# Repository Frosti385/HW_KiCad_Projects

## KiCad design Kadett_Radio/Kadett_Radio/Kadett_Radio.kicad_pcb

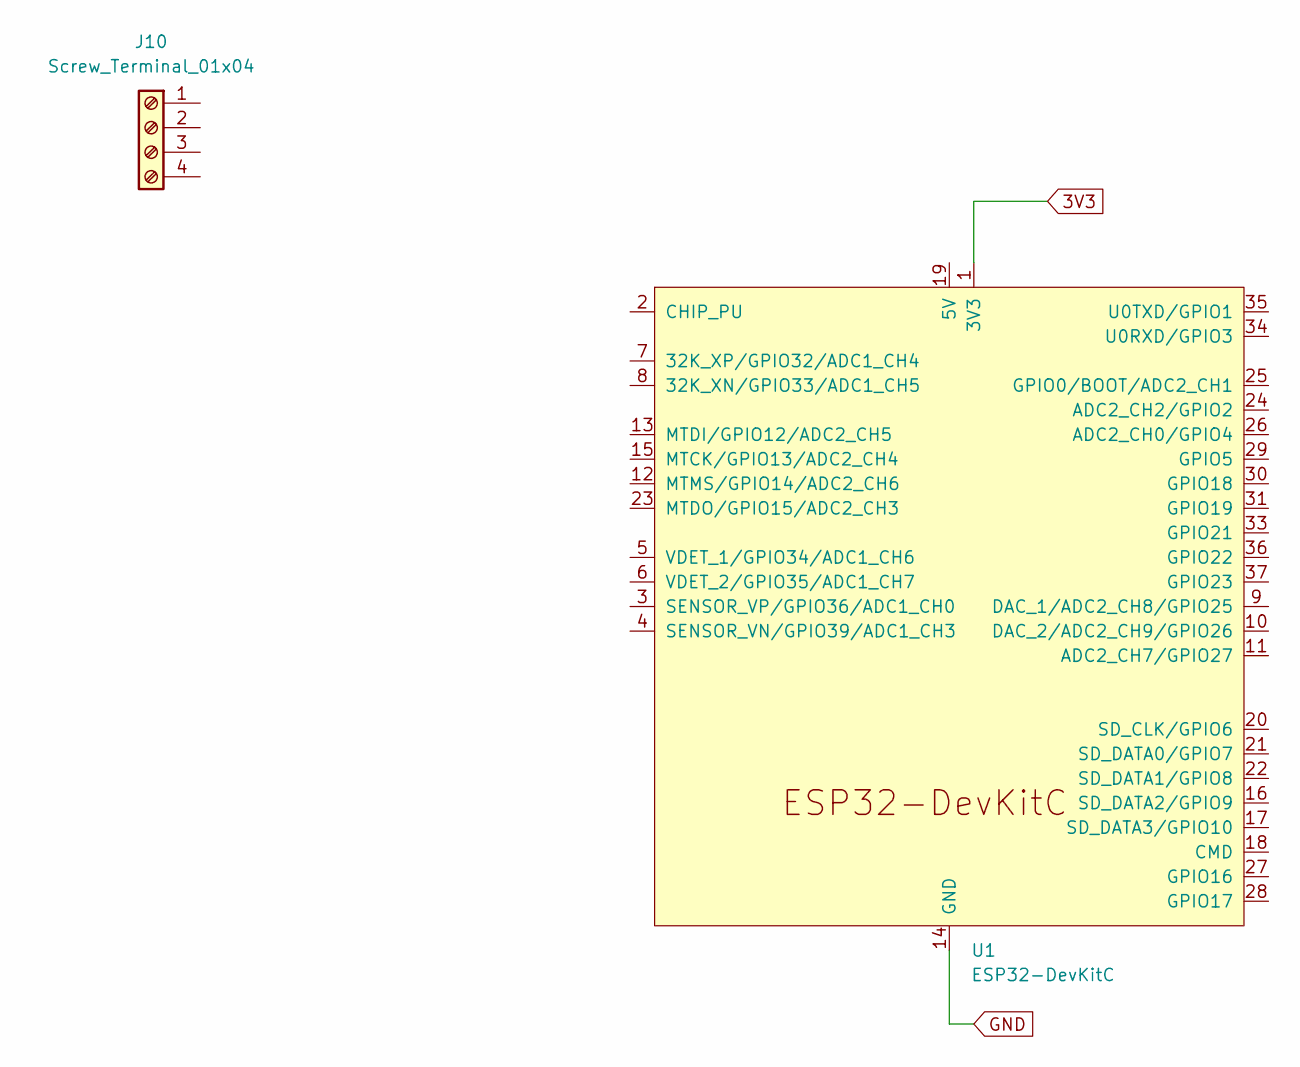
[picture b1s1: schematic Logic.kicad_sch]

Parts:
J10: Screw_Terminal_01x04; TerminalBlock_Phoenix_MPT-0,5-4-2.54_1x04_P2.54mm_Horizontal
U1: ESP32-DevKitC

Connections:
3V3: U1.1 (3V3); also elsewhere on the board
GND: U1.14 (GND), U1.32 (GND), U1.38 (GND); also elsewhere on the board

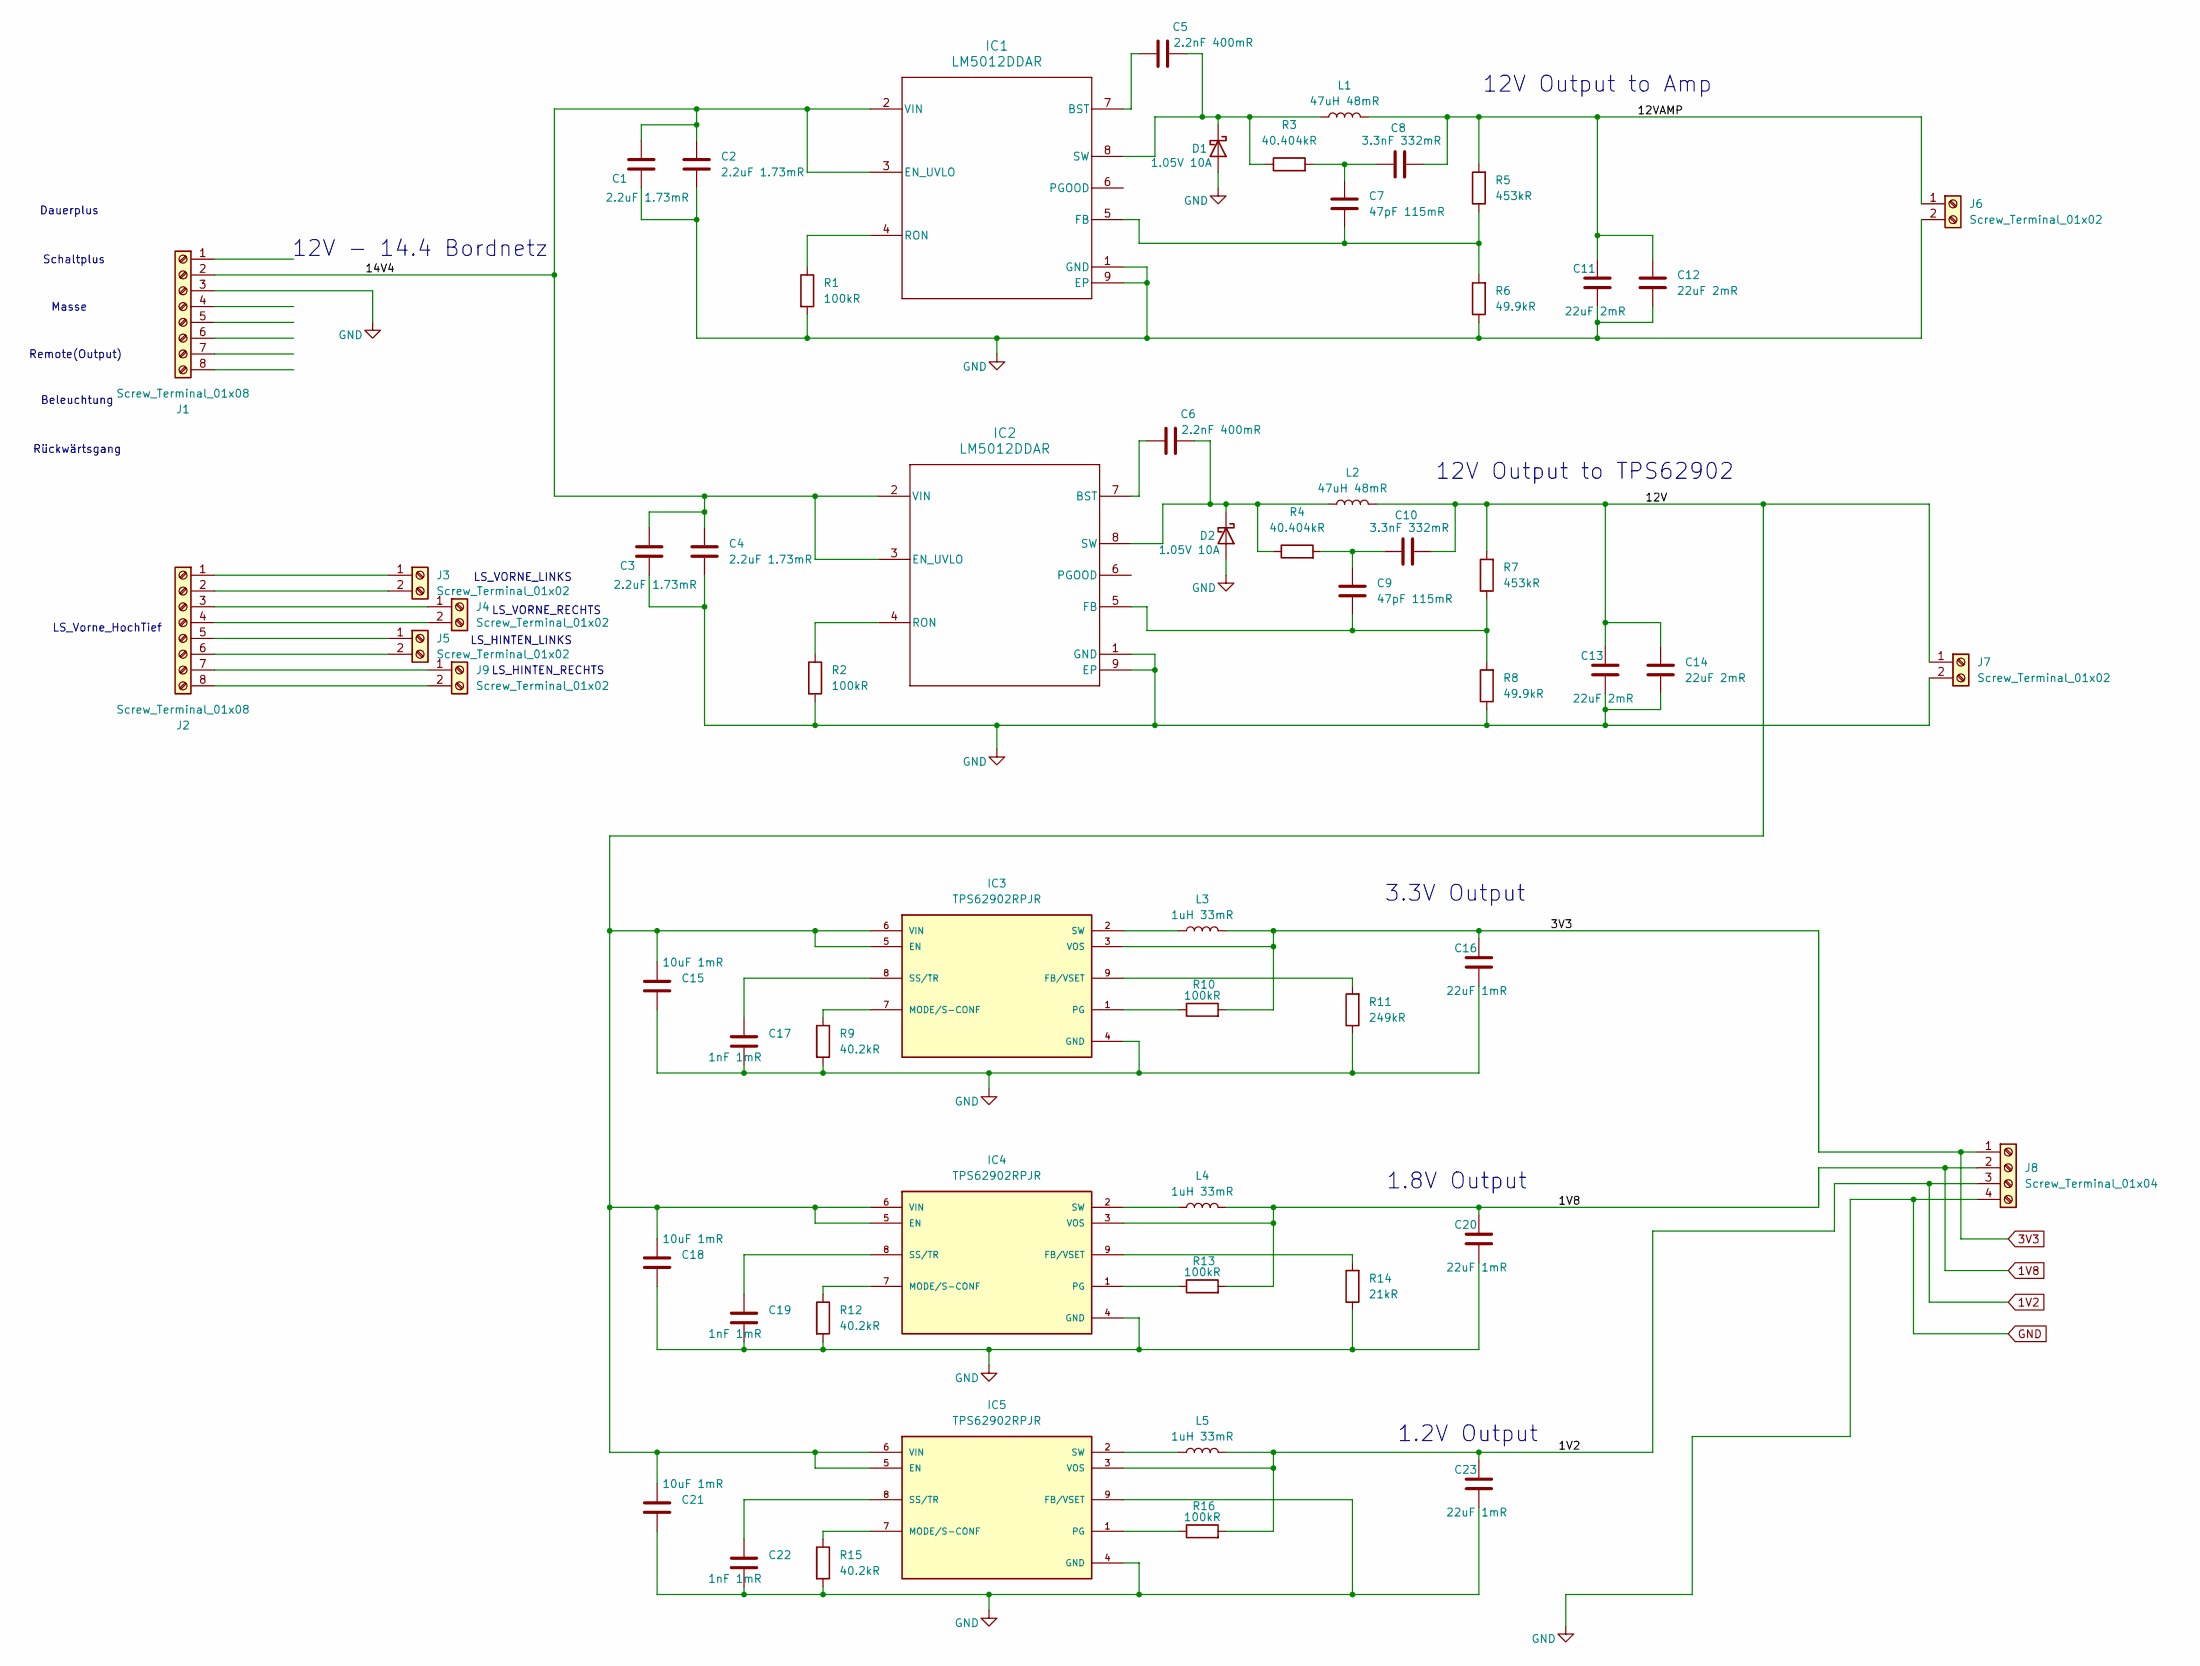
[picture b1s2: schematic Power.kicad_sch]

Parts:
C1, C2, C3, C4: 2.2uF 1.73mR; C_0603_1608Metric_Pad1.08x0.95mm_HandSolder
C5, C6: 2.2nF 400mR; C_0603_1608Metric_Pad1.08x0.95mm_HandSolder
C7, C9: 47pF 115mR; C_0603_1608Metric_Pad1.08x0.95mm_HandSolder
C8, C10: 3.3nF 332mR; C_0603_1608Metric_Pad1.08x0.95mm_HandSolder
C11, C12, C13, C14: 22uF 2mR; C_0603_1608Metric_Pad1.08x0.95mm_HandSolder
C15, C18, C21: 10uF 1mR; C_0603_1608Metric_Pad1.08x0.95mm_HandSolder
C16, C20, C23: 22uF 1mR; C_0603_1608Metric_Pad1.08x0.95mm_HandSolder
C17, C19, C22: 1nF 1mR; C_0603_1608Metric_Pad1.08x0.95mm_HandSolder
D1, D2: 1.05V 10A; D_0603_1608Metric_Pad1.05x0.95mm_HandSolder
IC1, IC2: LM5012DDAR; LM5012
IC3, IC4, IC5: TPS62902RPJR; PARTREV March 2021
J1, J2: Screw_Terminal_01x08; TerminalBlock_Phoenix_MPT-0,5-8-2.54_1x08_P2.54mm_Horizontal
J3, J4, J5, J6, J7, J9: Screw_Terminal_01x02; TerminalBlock_Phoenix_MPT-0,5-2-2.54_1x02_P2.54mm_Horizontal
J8: Screw_Terminal_01x04; TerminalBlock_Phoenix_MPT-0,5-4-2.54_1x04_P2.54mm_Horizontal
L1: 47uH 48mR; L_1206_3216Metric_Pad1.22x1.90mm_HandSolder
L2: 47uH 48mR; L_0603_1608Metric_Pad1.05x0.95mm_HandSolder
L3, L4, L5: 1uH 33mR; L_0603_1608Metric_Pad1.05x0.95mm_HandSolder
R1, R2, R10, R13, R16: 100kR; R_0603_1608Metric_Pad0.98x0.95mm_HandSolder
R3, R4: 40.404kR; R_0603_1608Metric_Pad0.98x0.95mm_HandSolder
R5, R7: 453kR; R_0603_1608Metric_Pad0.98x0.95mm_HandSolder
R6, R8: 49.9kR; R_0603_1608Metric_Pad0.98x0.95mm_HandSolder
R9, R12, R15: 40.2kR; R_0603_1608Metric_Pad0.98x0.95mm_HandSolder
R11: 249kR; R_0603_1608Metric_Pad0.98x0.95mm_HandSolder
R14: 21kR; R_0603_1608Metric_Pad0.98x0.95mm_HandSolder

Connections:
1V2: C23.2, IC5.3 (VOS), J8.3, L5.2, R16.2
1V8: C20.2, IC4.3 (VOS), J8.2, L4.2, R13.2
3V3: C16.2, IC3.3 (VOS), J8.1, L3.2, R10.2; also elsewhere on the board
/Power/12V: C10.2, C13.2, C14.2, C15.1, C18.1, C21.1, IC3.5 (EN), IC3.6 (VIN), IC4.5 (EN), IC4.6 (VIN), IC5.5 (EN), IC5.6 (VIN), J7.1, L2.2, R7.2
/Power/12VAMP: C8.2, C11.2, C12.2, J6.1, L1.2, R5.2
/Power/14V4: C1.1, C2.1, C3.1, C4.1, IC1.2 (VIN), IC1.3 (EN_UVLO), IC2.2 (VIN), IC2.3 (EN_UVLO), J1.2
GND: C1.2, C2.2, C3.2, C4.2, C11.1, C12.1, C13.1, C14.1, C15.2, C16.1, C17.2, C18.2, C19.2, C20.1, C21.2, C22.2, C23.1, D1.2 (A), D2.2 (A), IC1.1 (GND), IC1.9 (EP), IC2.1 (GND), IC2.9 (EP), IC3.4 (GND), IC4.4 (GND), IC5.4 (GND), IC5.9 (FB/VSET), J1.3, J6.2, J7.2, J8.4, R1.2, R2.2, R6.1, R8.1, R9.2, R11.1, R12.2, R14.1, R15.2; also elsewhere on the board
unnamed: C7.1, C8.1, R3.2
unnamed: C9.1, C10.1, R4.2
unnamed: C5.2, D1.1 (K), IC1.8 (SW), L1.1, R3.1
unnamed: C6.2, D2.1 (K), IC2.8 (SW), L2.1, R4.1
unnamed: C5.1, IC1.7 (BST)
unnamed: C7.2, IC1.5 (FB), R5.1, R6.2
unnamed: IC1.4 (RON), R1.1
unnamed: C6.1, IC2.7 (BST)
unnamed: C9.2, IC2.5 (FB), R7.1, R8.2
unnamed: IC2.4 (RON), R2.1
unnamed: IC3.9 (FB/VSET), R11.2
unnamed: IC3.7 (MODE/S-CONF), R9.1
unnamed: IC3.1 (PG), R10.1
unnamed: C17.1, IC3.8 (SS/TR)
unnamed: IC3.2 (SW), L3.1
unnamed: IC4.9 (FB/VSET), R14.2
unnamed: IC4.7 (MODE/S-CONF), R12.1
unnamed: IC4.1 (PG), R13.1
unnamed: C19.1, IC4.8 (SS/TR)
unnamed: IC4.2 (SW), L4.1
unnamed: IC5.7 (MODE/S-CONF), R15.1
unnamed: IC5.1 (PG), R16.1
unnamed: C22.1, IC5.8 (SS/TR)
unnamed: IC5.2 (SW), L5.1
unnamed: J2.1, J3.1
unnamed: J2.2, J3.2
unnamed: J2.3, J4.1
unnamed: J2.4, J4.2
unnamed: J2.5, J5.1
unnamed: J2.6, J5.2
unnamed: J2.7, J9.1
unnamed: J2.8, J9.2

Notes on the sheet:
12V Output to TPS62902
LS_VORNE_LINKS
Schaltplus
12V - 14.4 Bordnetz
1.8V Output
LS_HINTEN_LINKS
Beleuchtung
LS_VORNE_RECHTS
1.2V Output
Rückwärtsgang
LS_HINTEN_RECHTS
12V Output to Amp
Remote(Output)
3.3V Output
LS_Vorne_HochTief
Masse
Dauerplus

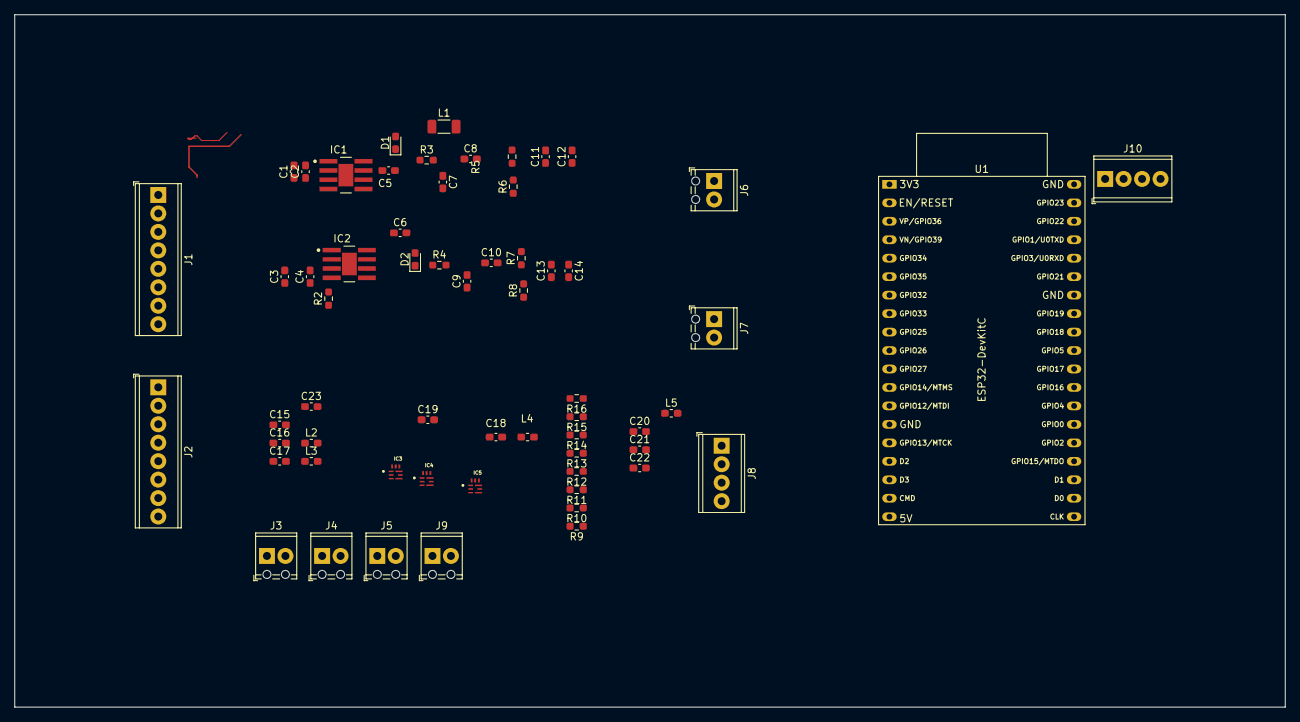
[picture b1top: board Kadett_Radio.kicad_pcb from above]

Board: 2 copper layers, 174.8 x 95.2 mm, 62 parts (1 on the bottom side), 39 nets.

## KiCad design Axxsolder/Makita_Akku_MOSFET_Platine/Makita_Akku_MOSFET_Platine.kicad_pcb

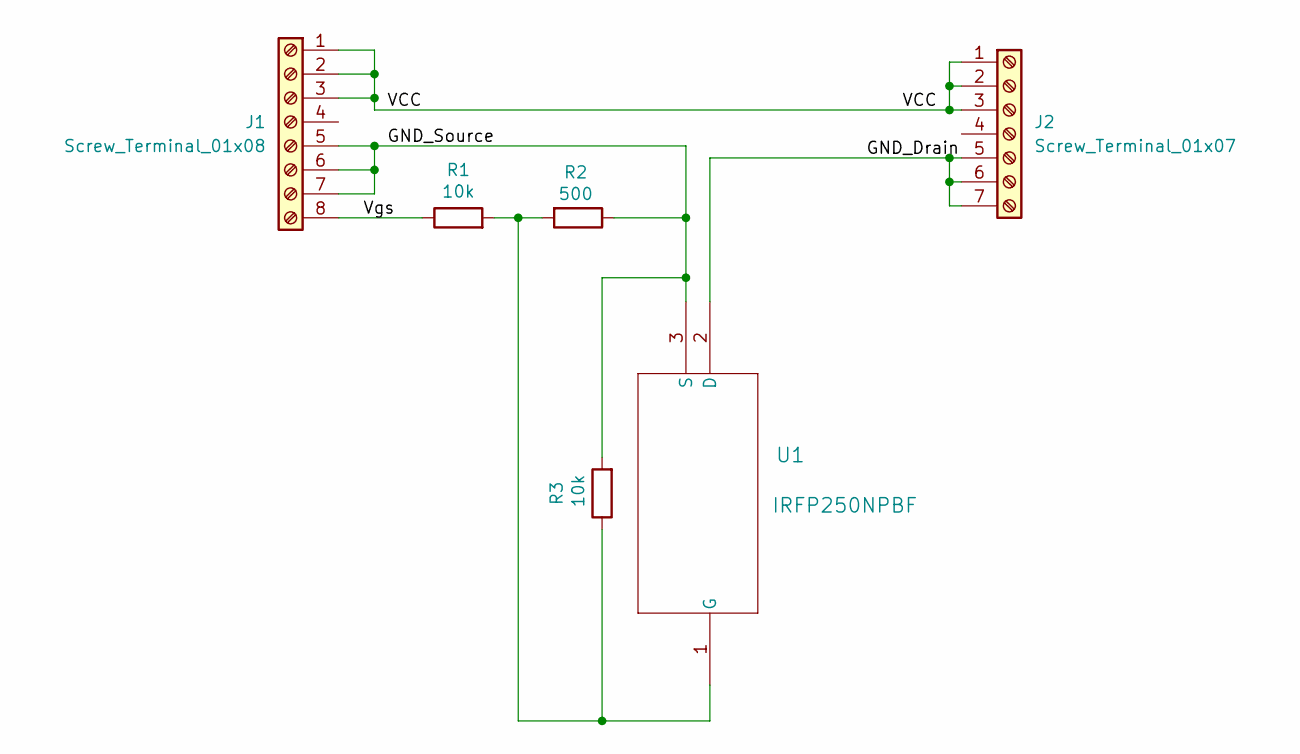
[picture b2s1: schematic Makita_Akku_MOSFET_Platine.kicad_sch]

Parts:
J1: Screw_Terminal_01x08; TerminalBlock_Phoenix_MPT-0,5-8-2.54_1x08_P2.54mm_Horizontal
J2: Screw_Terminal_01x07; TerminalBlock_Phoenix_MPT-0,5-7-2.54_1x07_P2.54mm_Horizontal
R1, R3: 10k; R_Axial_DIN0207_L6.3mm_D2.5mm_P7.62mm_Horizontal
R2: 500; R_Axial_DIN0207_L6.3mm_D2.5mm_P7.62mm_Horizontal
U1: IRFP250NPBF; IRFP250N

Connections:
/GND_Drain: J2.5, J2.6, J2.7, U1.2 (D)
/GND_Source: J1.5, J1.6, J1.7, R2.1, R3.2, U1.3 (S)
/VCC: J1.1, J1.2, J1.3, J2.1, J2.2, J2.3
/Vgs: J1.8, R1.1
unnamed: R1.2, R2.2, R3.1, U1.1 (G)

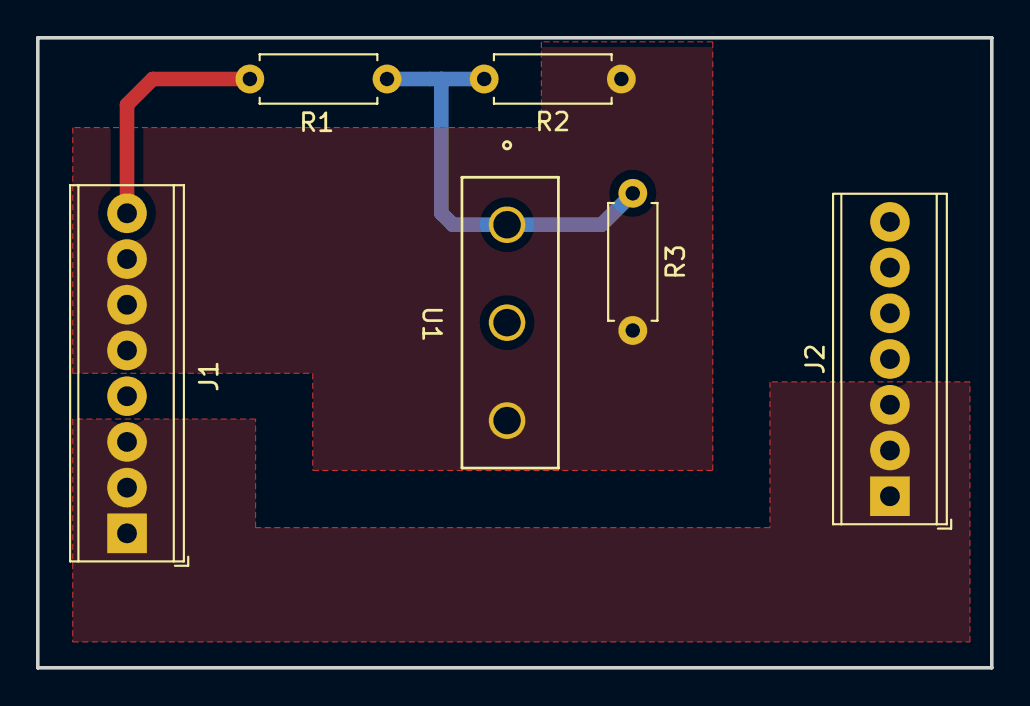
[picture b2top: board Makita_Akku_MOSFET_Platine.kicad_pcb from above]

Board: 4 copper layers, 53.0 x 35.0 mm, 6 parts (0 on the bottom side), 5 nets.

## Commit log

2024-06-18 feat: inital commit with project files
